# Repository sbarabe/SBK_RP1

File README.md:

# SBK_RP1

<p align="center">
  
  &nbsp;&nbsp;&nbsp;
  
</p>

<p align="center">
  <b>Front</b> &nbsp;&nbsp;&nbsp;&nbsp;&nbsp;&nbsp;&nbsp;&nbsp;&nbsp;&nbsp;&nbsp;&nbsp;&nbsp;&nbsp;&nbsp;&nbsp;&nbsp;&nbsp;&nbsp;&nbsp;&nbsp;&nbsp;&nbsp;&nbsp;&nbsp;&nbsp;&nbsp;
  <b>Back</b>
</p>

---

## Open-source reverse polarity protection module for learning and embedded electronics projects.

SBK_RP1 is a compact, reusable hardware module that protects low-voltage DC electronic circuits against accidental reverse battery connections. Using a P-channel MOSFET ideal-diode topology, it provides reverse polarity protection with a much lower voltage drop than a conventional series diode. An integrated LED indicates when protected output power is available.

Designed for breadboards, prototypes, and educational projects, SBK_RP1 offers a simple way to improve the robustness and reliability of battery-powered embedded systems.

---

## Features

- Input voltage: **2–12 VDC**
- Maximum Load current: **2 A**
- Maximum practical current depends on operating voltage, ambient temperature, PCB cooling, and allowable temperature rise.
- Reverse polarity protection using a **P-channel MOSFET**
- Very low forward voltage drop
- Protected output power status LED
- Breadboard-friendly 2.54 mm pin header
- Optimized for low-cost assembly using JLCPCB Basic components

---

## Pinout

| Pin | Description |
|------|-------------|
| **VIN** | Power input (2–12 VDC) |
| **GND** | Ground |
| **VOUT** | Protected power output |

---

## Typical Application

```text
Battery
   │
SBK_RP1
   │
SBK_SP1 (optional)
   │
Embedded System
```

SBK_RP1 is installed between the power source and the electronic circuit. During normal operation it introduces only a very small voltage drop. If the supply is accidentally connected in reverse, the module automatically blocks current, protecting the downstream electronics.

---

## Operation

1. Connect the power source to **VIN** and **GND**.
2. With correct polarity, the MOSFET turns on and powers **VOUT**.
3. The voltage drop across the module remains very low.
4. If the supply polarity is reversed, the MOSFET blocks sustained current flow to the protected output.
5. Current flow is blocked, protecting the connected circuit.
6. The output status LED indicates when protected power is present at **VOUT**.

---

## Applications

### Microcontroller platforms

- Arduino
- ESP32
- RP2040
- ATtiny
- STM32

### Example applications

- Battery-powered embedded systems
- Portable instruments
- Sensors
- Educational electronics projects
- Custom electronic devices

---

## Notes

- Designed for low-voltage DC electronic circuits.
- Protects against accidental reverse polarity connections.
- Does not provide over-current or over-voltage protection.
- The output status LED indicates the presence of protected output voltage; it is not a reverse polarity indicator.

---

## Getting Started

This project is fully open-source hardware. You can:

- Build your own module using the provided KiCad design files.
- Modify the design to suit your application.
- Manufacture your own boards.

### Assembled Modules

If you prefer a ready-to-use module, fully assembled SBK_SP1 boards may be available in small batches on demand.

For availability, pricing, or quantity inquiries, contact:

📧 **SmartBuildsKits@gmail.com**

These modules are intended for hobbyists, educators, prototypes, and small-scale projects. Availability depends on component stock and production capacity.

---

## Related Projects

- [**SBK_FET1**](https://github.com/sbarabe/SBK_FET1) – N-Channel/P-Channel FET modules
- [**SBK_SP1**](https://github.com/sbarabe/SBK_SP1) – Soft Power Switch Module
- [**MémoBot**](https://github.com/sbarabe/MemoBot) – Educational memory game built using SBK_SP1 and SBK_RP1

---

## Contributing

Suggestions, bug reports, and improvements are welcome.

To report a problem or suggest an improvement, open an Issue. Pull Requests are also welcome for corrections, documentation improvements, and design changes that make the project easier to understand or build.

---

## Support the Project

If this project is useful for learning, teaching, or prototyping, you can support its continued development.

Donations help fund prototype hardware, documentation, educational resources, and future open-source projects.

❤️ [**Support the project through PayPal**](https://paypal.me/sbarab?country.x=CA&locale.x=fr_CA)

Thank you for supporting open-source educational hardware.

---

## License

This project is released as open-source hardware under the **CERN Open Hardware Licence Version 2 - Permissive (CERN-OHL-P v2)**.

You are free to study, modify, manufacture, and distribute this design, provided the terms of the license are respected.

See the [LICENSE](LICENSE) file for the full license text.

---

## Design Files

This project was designed using **KiCad 10**.

- [KiCad hardware files](hardware/)
- [Bill of materials](hardware/bom.csv)
- [SBK_RP1 datasheet](docs/SBK_RP1_datasheet.pdf)

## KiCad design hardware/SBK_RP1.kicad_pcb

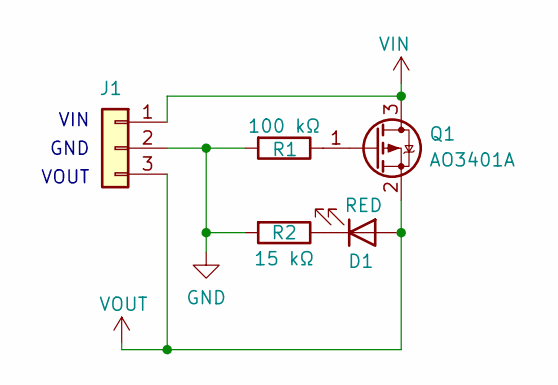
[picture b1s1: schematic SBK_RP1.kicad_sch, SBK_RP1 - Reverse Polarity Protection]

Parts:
D1: RED; LED_0603_1608Metric
J1: 1 x 3 pin header; PinHeader_1x03_P2.54mm_Vertical
Q1: AO3401A; SOT-23
R1: 100 kΩ; R_0603_1608Metric
R2: 15 kΩ; R_0402_1005Metric

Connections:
GND: J1.2, R1.2, R2.2
unnamed: D1.1 (K), R2.1
unnamed: Q1.1 (G), R1.1
VIN: J1.1, Q1.3 (D)
VOUT: D1.2 (A), J1.3, Q1.2 (S)

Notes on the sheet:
GND
VOUT
VIN

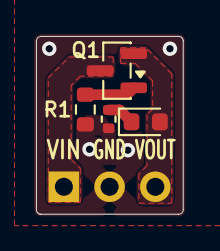
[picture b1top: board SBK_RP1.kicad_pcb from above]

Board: 2 copper layers, 8.2 x 9.9 mm, 5 parts (1 on the bottom side), 5 nets.

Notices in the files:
hardware/SBK_RP1.kicad_sch:
Licensed under CERN-OHL-P-2.0
